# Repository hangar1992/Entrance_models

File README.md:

# Entrance_models
Entrance_models

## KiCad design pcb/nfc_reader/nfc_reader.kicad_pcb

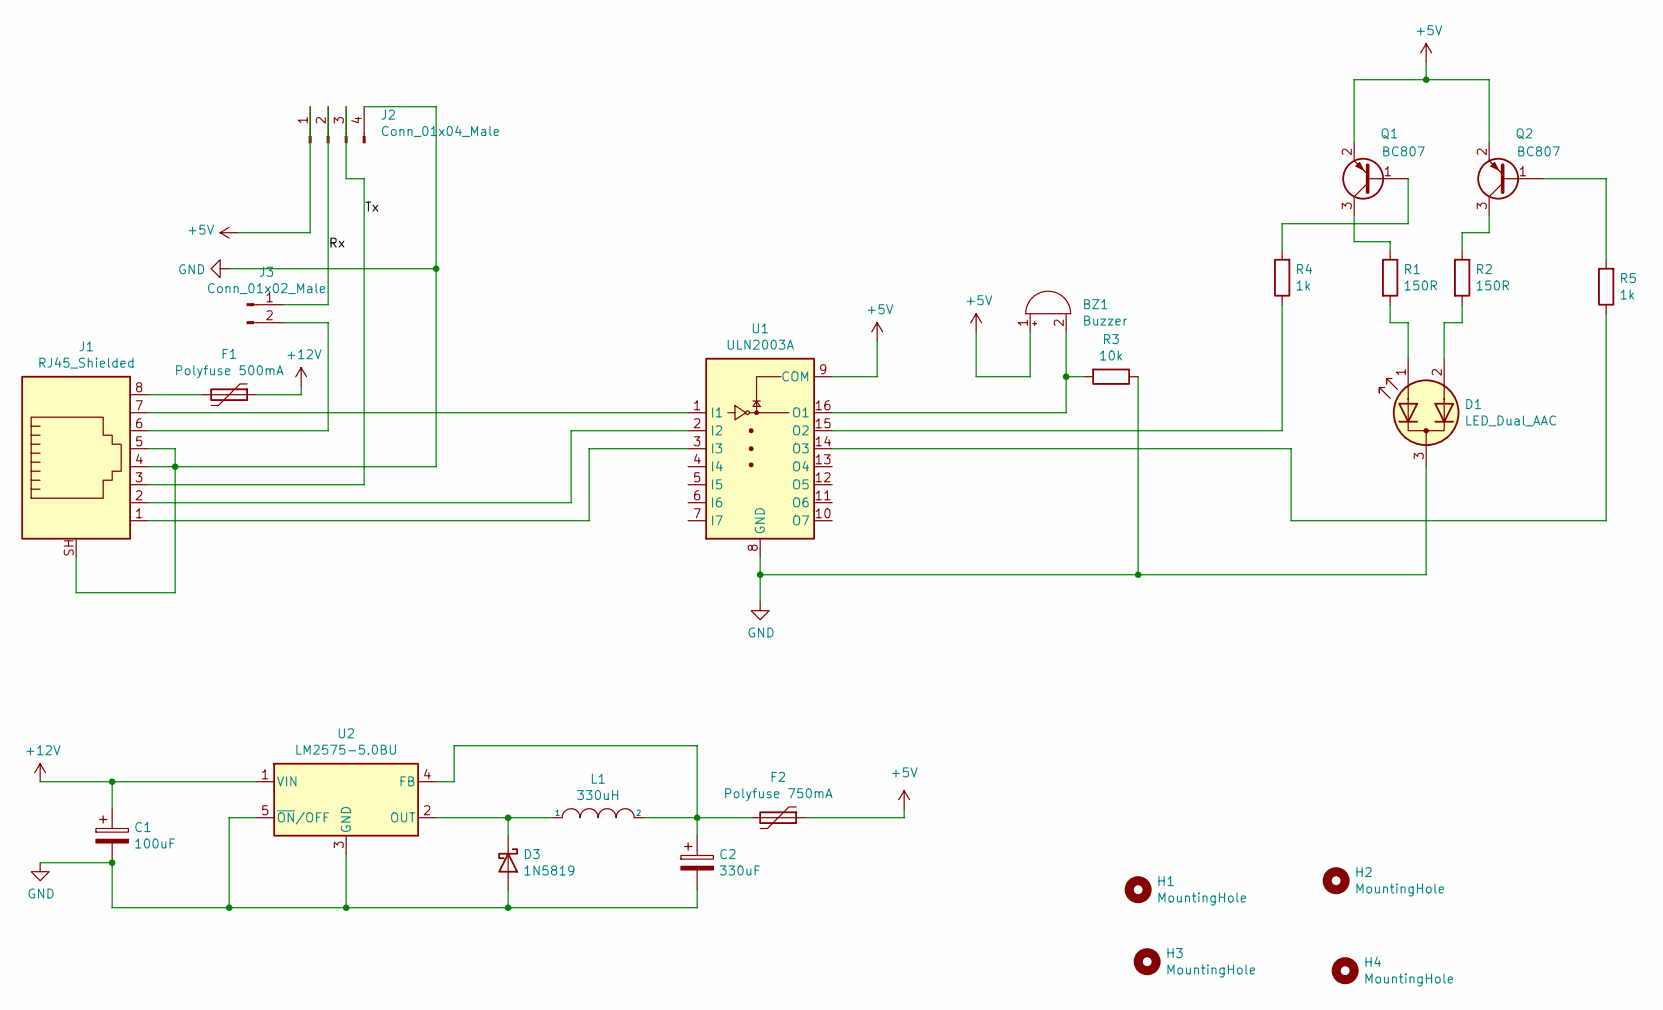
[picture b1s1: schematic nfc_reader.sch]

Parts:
BZ1: Buzzer; Buzzer_12x9.5RM7.6
C1: 100uF; CP_Elec_6.3x7.7
C2: 330uF; CP_EIA-7343-31_Kemet-D
D1: LED_Dual_AAC; PinHeader_1x03_P2.54mm_Horizontal
D3: 1N5819; D_MELF
F1: Polyfuse 500mA; Fuse_Littelfuse_395Series
F2: Polyfuse 750mA; Fuse_Littelfuse_395Series
H1, H2, H3, H4: MountingHole; MountingHole_3.2mm_M3_ISO7380
J1: RJ45_Shielded; RJ45_Ninigi_GE
J2: Conn_01x04_Male; PinHeader_1x04_P2.54mm_Horizontal
J3: Conn_01x02_Male; PinHeader_1x02_P2.54mm_Vertical
L1: 330uH; WE-PD-SMD-INDUCTOR
Q1, Q2: BC807; SOT-23
R1, R2: 150R; R_1206_3216Metric
R3: 10k; R_0805_2012Metric
R4, R5: 1k; R_0805_2012Metric
U1: ULN2003A; SO-16_3.9x9.9mm_P1.27mm
U2: LM2575-5.0BU; TO-263-5_TabPin3

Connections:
+5V: BZ1.1 (-), F2.1, J2.1, Q1.2 (E), Q2.2 (E), U1.9 (COM)
+12V: C1.1, F1.1, U2.1 (VIN)
/Rx: J2.2, J3.1
/Tx: J1.3, J2.3
GND: C1.2, C2.2, D1.3 (K), D3.2 (A), J1.4, J1.5, J1.SH, J2.4, R3.1, U1.8 (GND), U2.3 (GND), U2.5 (~ON~/OFF)
unnamed: BZ1.2 (+), R3.2, U1.16 (O1)
unnamed: C2.1, F2.2, L1.2, U2.4 (FB)
unnamed: D1.1 (A1), R1.2
unnamed: D1.2 (A2), R2.2
unnamed: D3.1 (K), L1.1, U2.2 (OUT)
unnamed: F1.2, J1.8
unnamed: J1.1, U1.3 (I3)
unnamed: J1.2, U1.2 (I2)
unnamed: J1.6, J3.2
unnamed: J1.7, U1.1 (I1)
unnamed: Q1.1 (B), R4.2
unnamed: Q1.3 (C), R1.1
unnamed: Q2.1 (B), R5.2
unnamed: Q2.3 (C), R2.1
unnamed: R4.1, U1.15 (O2)
unnamed: R5.1, U1.14 (O3)

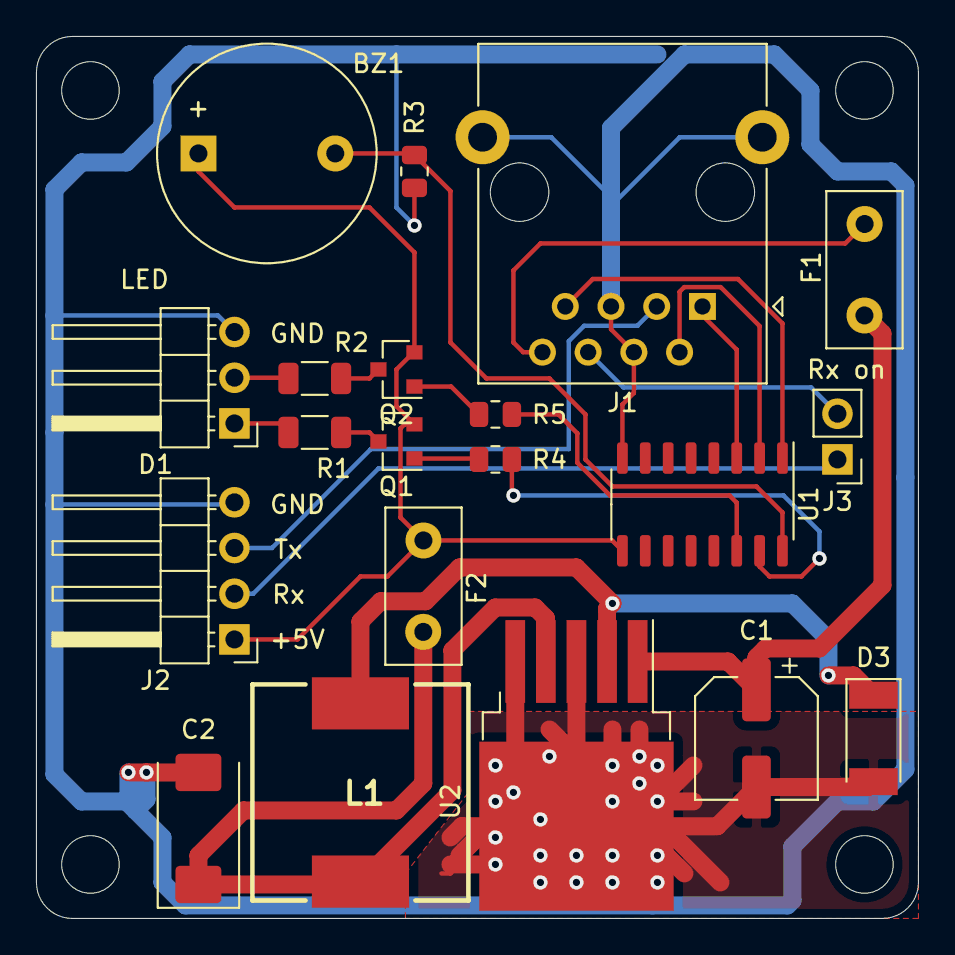
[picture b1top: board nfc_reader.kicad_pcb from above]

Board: 2 copper layers, 49.0 x 49.0 mm, 24 parts (0 on the bottom side), 21 nets.

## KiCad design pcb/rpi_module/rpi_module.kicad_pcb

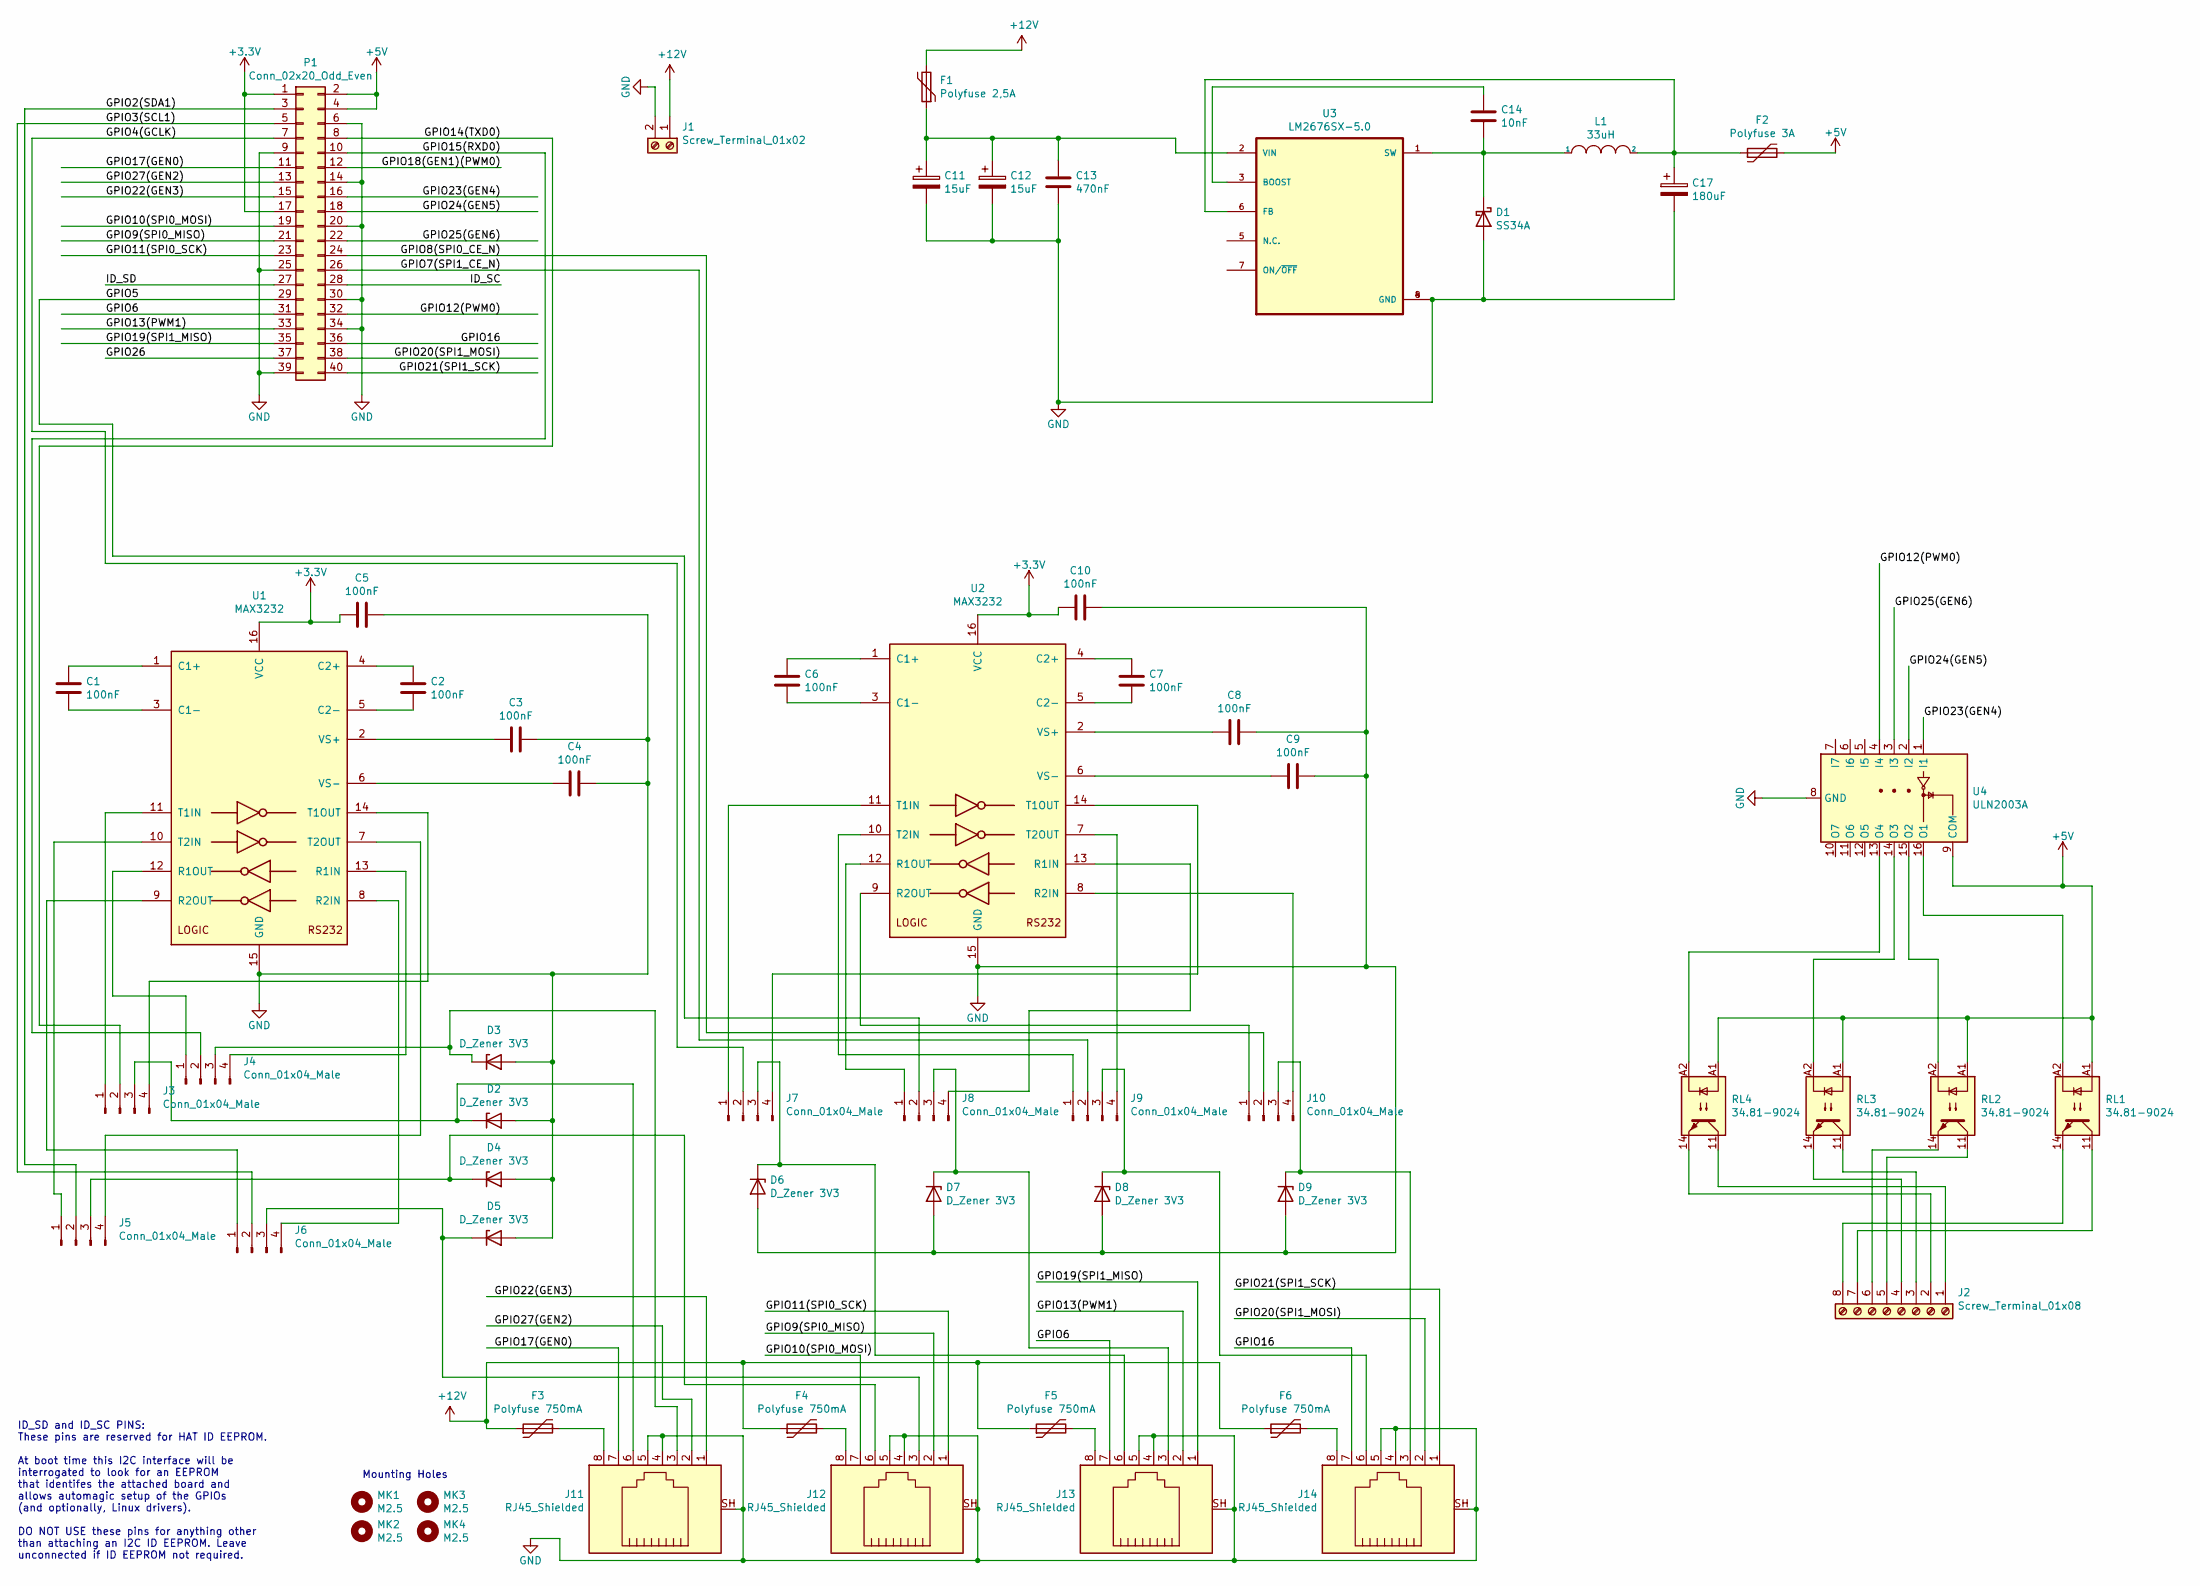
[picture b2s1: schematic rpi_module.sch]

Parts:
C1, C2, C3, C4, C5, C6, C7, C8, C9, C10: 100nF; C_0603_1608Metric
C11, C12: 15uF; CP_EIA-7343-31_Kemet-D
C13: 470nF; C_1206_3216Metric
C14: 10nF; C_0603_1608Metric
C17: 180uF; CP_EIA-7343-31_Kemet-D
D1: SS34A; D_SMA
D2, D3, D4, D5, D6, D7, D8, D9: D_Zener 3V3; D_SOD-123
F1: Polyfuse 2,5A; Fuse_Littelfuse_395Series
F2: Polyfuse 3A; Fuse_Littelfuse_395Series
F3, F4, F5, F6: Polyfuse 750mA; Fuse_Littelfuse_395Series
J1: Screw_Terminal_01x02; TE_282815-2
J2: Screw_Terminal_01x08; TE_284513-8
J3, J4, J5, J6, J7, J8, J9, J10: Conn_01x04_Male; PinHeader_1x04_P2.54mm_Vertical
J11, J12, J13, J14: RJ45_Shielded; RJ45_Ninigi_GE
L1: 33uH; INDPM120120X600N
MK1, MK2, MK3, MK4: M2.5; MountingHole_3.2mm_M3_DIN965_Pad
P1: Conn_02x20_Odd_Even; PinSocket_2x20_P2.54mm_Vertical
RL1, RL2, RL3, RL4: 34.81-9024; SSR_Relay_Cosmo_KSD215AC3
U1, U2: MAX3232; SO-16_3.9x9.9mm_P1.27mm
U3: LM2676SX-5.0; TO127P1435X464-8N
U4: ULN2003A; SO-16_3.9x9.9mm_P1.27mm

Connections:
+3V3: C5.2, C10.2, P1.1, P1.17, U1.16 (VCC), U2.16 (VCC)
+5V: F2.2, P1.2, P1.4, RL1.A1, RL2.A1, RL3.A1, RL4.A1, U4.9 (COM)
+12V: F1.2, F3.1, F4.1, F5.1, F6.1, J1.1
/GPIO2(SDA1): J5.2, P1.3
/GPIO3(SCL1): J6.2, P1.5
/GPIO4(GCLK): J7.2, P1.7
/GPIO5: J8.2, P1.29
/GPIO6: J13.7, P1.31
/GPIO7(SPI1_CE_N): J9.2, P1.26
/GPIO8(SPI0_CE_N): J10.2, P1.24
/GPIO9(SPI0_MISO): J12.2, P1.21
/GPIO10(SPI0_MOSI): J12.7, P1.19
/GPIO11(SPI0_SCK): J12.1, P1.23
/GPIO12(PWM0): P1.32, U4.4 (I4)
/GPIO13(PWM1): J13.2, P1.33
/GPIO14(TXD0): J3.2, P1.8
/GPIO15(RXD0): J4.2, P1.10
/GPIO16: J14.7, P1.36
/GPIO17(GEN0): J11.7, P1.11
/GPIO18(GEN1)(PWM0): P1.12
/GPIO19(SPI1_MISO): J13.1, P1.35
/GPIO20(SPI1_MOSI): J14.2, P1.38
/GPIO21(SPI1_SCK): J14.1, P1.40
/GPIO22(GEN3): J11.1, P1.15
/GPIO23(GEN4): P1.16, U4.1 (I1)
/GPIO24(GEN5): P1.18, U4.2 (I2)
/GPIO25(GEN6): P1.22, U4.3 (I3)
/GPIO26: P1.37
/GPIO27(GEN2): J11.2, P1.13
/ID_SC: P1.28
/ID_SD: P1.27
GND: C3.1, C4.1, C5.1, C8.1, C9.1, C10.1, C11.2, C12.2, C13.1, C17.2, D1.2 (A), D2.2 (A), D3.2 (A), D4.2 (A), D5.2 (A), D6.2 (A), D7.2 (A), D8.2 (A), D9.2 (A), J1.2, J11.4, J11.5, J11.SH, J12.4, J12.5, J12.SH, J13.4, J13.5, J13.SH, J14.4, J14.5, J14.SH, P1.6, P1.9, P1.14, P1.20, P1.25, P1.30, P1.34, P1.39, U1.15 (GND), U2.15 (GND), U3.4 (GND), U3.8 (GND), U4.8 (GND)
unnamed: C1.1, U1.1 (C1+)
unnamed: C1.2, U1.3 (C1-)
unnamed: C2.1, U1.4 (C2+)
unnamed: C2.2, U1.5 (C2-)
unnamed: C3.2, U1.2 (VS+)
unnamed: C4.2, U1.6 (VS-)
unnamed: C6.1, U2.1 (C1+)
unnamed: C6.2, U2.3 (C1-)
unnamed: C7.1, U2.4 (C2+)
unnamed: C7.2, U2.5 (C2-)
unnamed: C8.2, U2.2 (VS+)
unnamed: C9.2, U2.6 (VS-)
unnamed: C11.1, C12.1, C13.2, F1.1, U3.2 (VIN)
unnamed: C14.1, D1.1 (K), L1.1, U3.1 (SW)
unnamed: C14.2, U3.3 (BOOST)
unnamed: C17.1, F2.1, L1.2, U3.6 (FB)
unnamed: D2.1 (K), J3.3, J11.6
unnamed: D3.1 (K), J4.3, J11.3
unnamed: D4.1 (K), J5.3, J12.6
unnamed: D5.1 (K), J6.3, J12.3
unnamed: D6.1 (K), J7.3, J13.6
unnamed: D7.1 (K), J8.3, J13.3
unnamed: D8.1 (K), J9.3, J14.6
unnamed: D9.1 (K), J10.3, J14.3
unnamed: F3.2, J11.8
unnamed: F4.2, J12.8
unnamed: F5.2, J13.8
unnamed: F6.2, J14.8
unnamed: J2.1, RL4.11
unnamed: J2.2, RL4.14
unnamed: J2.3, RL3.11
unnamed: J2.4, RL3.14
unnamed: J2.5, RL2.11
unnamed: J2.6, RL2.14
unnamed: J2.7, RL1.11
unnamed: J2.8, RL1.14
unnamed: J3.1, U1.11 (T1IN)
unnamed: J3.4, U1.14 (T1OUT)
unnamed: J4.1, U1.12 (R1OUT)
unnamed: J4.4, U1.13 (R1IN)
unnamed: J5.1, U1.10 (T2IN)
unnamed: J5.4, U1.7 (T2OUT)
unnamed: J6.1, U1.9 (R2OUT)
unnamed: J6.4, U1.8 (R2IN)
unnamed: J7.1, U2.11 (T1IN)
unnamed: J7.4, U2.14 (T1OUT)
unnamed: J8.1, U2.12 (R1OUT)
unnamed: J8.4, U2.13 (R1IN)
unnamed: J9.1, U2.10 (T2IN)
unnamed: J9.4, U2.7 (T2OUT)
unnamed: J10.1, U2.9 (R2OUT)
unnamed: J10.4, U2.8 (R2IN)
unnamed: RL1.A2, U4.16 (O1)
unnamed: RL2.A2, U4.15 (O2)
unnamed: RL3.A2, U4.14 (O3)
unnamed: RL4.A2, U4.13 (O4)

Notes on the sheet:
ID_SD and ID_SC PINS: These pins are reserved for HAT ID EEPROM. At boot time this I2C interface will be interrogated to look for an EEPROM that identifes the attached board and allows automagic setup of the GPIOs (and optionally, Linux drivers). DO NOT USE these pins for anything other than attach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
Mounting Holes

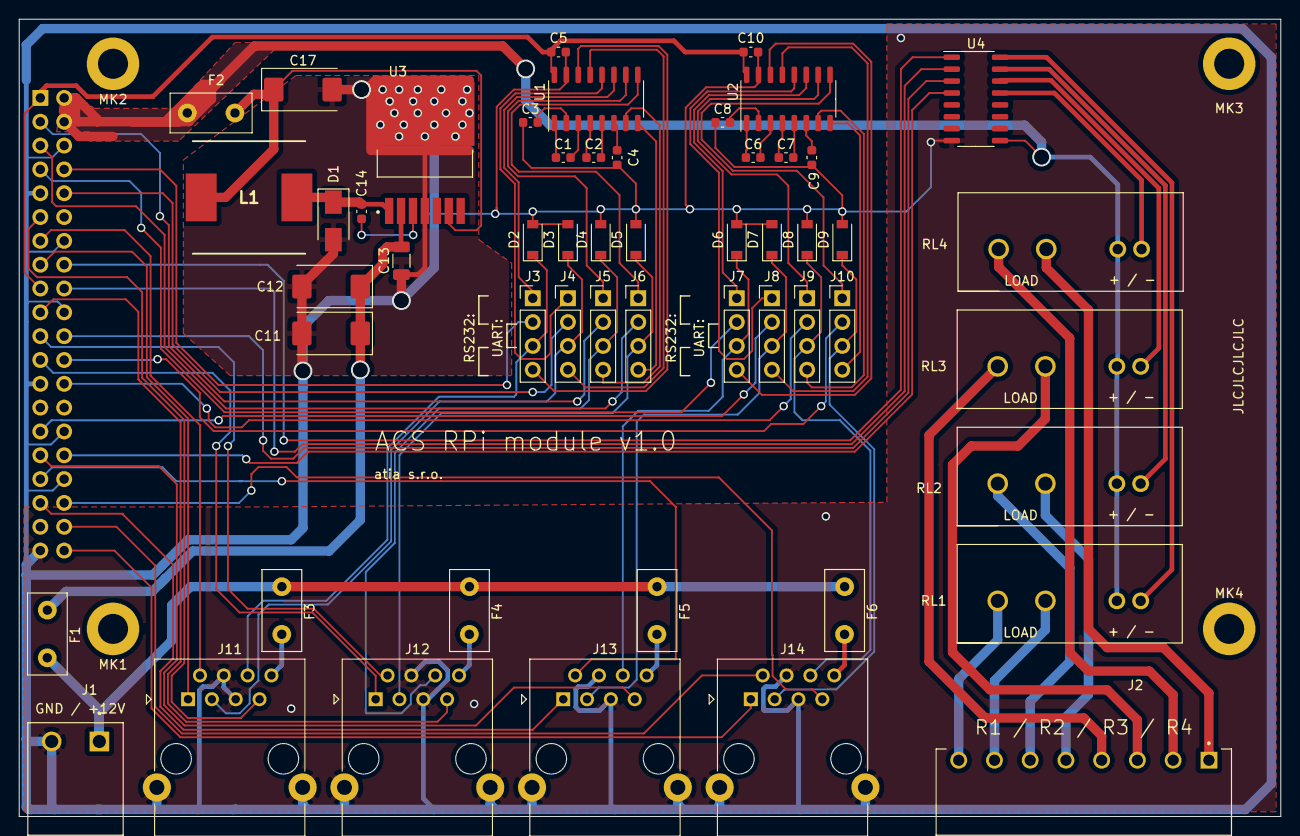
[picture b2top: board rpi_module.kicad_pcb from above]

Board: 2 copper layers, 134.5 x 85.0 mm, 58 parts (1 on the bottom side), 84 nets.

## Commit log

2020-11-25 Pridane prvni verze (netestovane) modelu
2020-11-29 Change RPi bottom box, added slicer factory file for NFC reader box (bottom)
2020-11-29 NFC reader placement change (collision with LED)
2021-02-28 Pridan factory file k 3D tisku
2021-02-28 Pridany design soubory PCB + vyrobni podklady
2021-02-28 Presunuty stare 3D modely (jiz nepouzivane)
2021-02-28 Pridany rozdelane modely pro novou QR ctecku (prototyp, neni final)
2021-03-28 Pridany posledni verze modelu
2021-05-01 Pridana PCB pro NFC ctecku
